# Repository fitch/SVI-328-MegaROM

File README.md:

# SVI-328 MegaROM

## Overview

This is a 1024 kB (8 megabit) ROM cartridge for Spectravideo 328 that fits into a standard SVI-328 game cartridge slot without any hardware modifications.

The implementation is based on Timo Soilamaa's idea on having a CD4060 binary counter chip with a built-in oscillator to control high address lines of a large memory chip. This version exposes a 16 kB window of a larger 1024 kB at time to SVI-328 and changes the window to the next after a while has passed. A more thorough explanation on how it works is found in chapter [The hardware](#the-hardware) and [Cartridge ROM contents and operation](#cartridge-rom-contents-and-operation).

## Contents

This repository contains:
 - The source code for the ROM code (a game launcher) that can be burned into an EPROM memory chip.
 - The schematics and the layout of the PCB, which can be manufactured, for example, using [PCBWay](https://www.pcbway.com).
 - A tool (embedded to the makefile) that packs and chunks games into a format that the game launcher can handle on the device.

## System requirements

The implementation has been tested with macOS Sonoma 14.6.1 and requires the following software to be installed, and found from path when executing the `makefile`:
 - [z88dk version 2.3](https://github.com/z88dk/z88dk) (currently only z88dk-z80asm is used)
 - [openMSX emulator version 20.0](https://openmsx.org) (which should be installed in /Applications/openMSX.app)
 - [Node.js version 22.12.10](https://nodejs.org/en) or newer
 - [zx0 version 2.2](https://github.com/einar-saukas/ZX0)
 - [GNU M4](https://www.gnu.org/software/m4) (it should come with [Xcode](https://apps.apple.com/us/app/xcode/id497799835?mt=12) command line developer tools, tested with version 1.4.6)

## I don't have time to read this all :) 

Follow these instructions to get a version up and running in openMSX emulator.

### Create the ROM metadata

When you have installed the previous programs, get a ready 32 kB ROM image like Frantic Freddy, review [roms/roms.json.example](roms/roms.json.example) and create `roms/roms.json` with the following content:

    [
        {
            "name": "Frantic Freddy",
            "author": "Spectravideo",
            "file": "franticfreddy.rom.32.dat.zx0",
            "type": "rom.32.zx0",
            "jump": "0x000c",
            "crc16": "0x9c06"
        }
    ]

You can place the ROM image to `uncompressed_roms` folder with file name `franticfreddy.rom.32.dat` and then run `./calculate_crc16.sh` to see if the crc16 matches the example above. If it does, you're using the correct ROM image.

### Compress the ROM data

Now compress the ROM image using zx0 with `zx0 franticfreddy.rom.32.dat`. You should see something like this:

```
ZX0 v2.2: Optimal data compressor by Einar Saukas
[...............................................]
File compressed from 32768 to 8363 bytes! (delta 2)
```

Move `franticfreddy.rom.32.dat.zx0` to [roms](roms/) folder.

### Compile and run

Now, create an emulator version of the ROM image with `make emulator`.

Then, use `make run` to run the version in openMSX emulator.

### Load the game

You should now see the game selector on screen. Press A to load the game and then navigate to Memory debugger to do the following (to simulate the changing ROM window):
 - Write 0x01 to address 0x8000
 - Write 0x00 to address 0x8000
 - Write 0x01 to address 0x8000

The game should now load.

# The hardware

The cartridge design in inspired by [Noel Llopis' 32 kB cartridge](https://github.com/llopis/SVI328-ROM-Cartridge) for Spectravideo 328. The physical design, however, differs so that the edge connector is now exactly 40 mm wide making it align with the cartridge slot better.

The cartridge has the following components:
 - J1: A 30 pin edge connector that will fit the Spectravideo 328 cartridge slot
 - U1: An EPROM memory chip 27C080 (a UV EPROM version of the [AT27C080](https://ww1.microchip.com/downloads/en/DeviceDoc/doc0360.pdf)) 1024 kB (8 megabit)
 - U2: A 14-stage ripple-carry binary counter and oscillator chip CD4060 ([CD4060BE](https://www.ti.com/lit/ds/symlink/cd4060b.pdf))
 - R1: A 68 kΩ resistor, R2: A 1 kΩ resistor and C2: A 0.1 μF capacitor to provide the CD4060 1 / ( 2.3 * 0.0000001 F * 68000 Ω) = 63.93861893 Hz frequency to the oscillator, making Q3 go high after 8 clock cycles in ~125 milliseconds which is the rotation speed for the ROM windows
 - C1: A 0.1 μF capacitor acts as the decoupling capacitor to remove common noise and transient conditions

See chapter [Sector rotation](#sector-rotation) for information on how the CD4060 operates with the 27C080.

I recommend using a 32-pin spring socket under the memory chip so that it's easy to detach and attach the EPROMs.

# Cartridge ROM contents and operation

## Sector structure

The 1024 kB ROM memory is divided into 64 16384 byte sections (sectors), which consist of the following main parts:
1. The [loader](asm/loader.asm) (currently 16 bytes)
2. The sector data
3. The sector identifier (one byte, the last one in the sector)

Sector 0 (the first sector) contains the following functionality in the sector data (2.) section:
 - [decompressor](asm/decompressor.asm) which sets up the zx0 decompressor in high RAM (`DZX0_ADDRESS`) and also copies the launcher to high RAM (`LAUNCHER_ADDRESS`, see [makefile](makefile) for the values)
 - [launcher](asm/launcher.asm) which displays the game selector, chooses the right game loader and executes the game loading sequence and starts the game

Other sectors (from 1 to 63) contain the game data. This will be explained in chapter [Game data](#game-data).

## Sector rotation

The 1024 kB of a 27C080 is accessed via address lines A0..A19 (2^20 bytes) the following way:
 - The SVI-328 cartridge connector addressess directly the first A0..A13 (2^14 = 16384) bytes when Cartridge ROM bank (bank xx, when /CART is low) is accessed from memory addressess 0x0000 - 0x3fff.
 - Accessing these addresses will also set /CCS1 line low. This line is used to enable the 27C080 memory chip using /OE (output enable) and /CE (chip enable).
 - The CD4060 counter chip coordinates address lines A14 to A19.

The binary counter starts from 0, when all the Qx lines are low (zero). After 8 clock cycles line Q3 goes high (~125 ms) and sets A14 high (1). This will make the 270C080 address pointer point to the 2nd 16 kB block and so on. Cycling through all the 16 kB sectors takes ~8 seconds in this configuration.

As each of the sectors contain the sector identifier byte (starting from 0x00 in sector 0, continuing as 0x01 in sector 1 and so on), you can always check which sector is visible by reading the memory address 0x3fff (when bank xx is selected by setting /CART low [using the PSG](asm/launcher/psg.asm)).

The ~125 ms rotation speed is based on that then the CPU has enough time to read the 16 kB of sector data and write it to RAM using [FastLDIR](asm/launcher/fast_ldir.asm) memory copying function.

## Boot up procedure

When the SVI-328 is booted up with the cartridge ROM attached, it follows these phases:

1. When a cartridge ROM is attached, /CART is set low and the memory bank mapping the cartridge ROM contents to 0x0000 - 0x7fff is enabled. (However, we will only use the first 16 kB between 0x0000 - 0x3fff, the contents between 0x4000 - 0x7fff are undefined.)
2. The [loader](asm/loader.asm) is visible at memory address 0x0000 (every sector starts with the loader, so it's always visible at this address). The loader starts with `di` and `ld sp, xxxx` instructions which instructs the SVI-328 that we have a valid cartridge ROM attached.
3. The loader waits until sector 0 has passed (not displaying sector 0) and then waits again until sector 0 is visible again. This is to ensure that the CPU will have enough time to copy the launcher from sector 0 to RAM.
4. Next, the [decompressor](asm/decompressor.asm) will copy the zx0 decompressor to end of RAM at address `DZX0_ADDRESS` (so it won't get overwritten later) and also a compressed copy of the [launcher](asm/launcher.asm) to address 0xc000. Then, the launcher is decompressed to address `LAUNCHER_ADDRESS`.
5. At last, the launcher execution is started in RAM at address `LAUNCHER_ADDRESS`.

## Launcher

The [launcher](asm/launcher.asm) consists of the following sections:

1. [Splash screen](asm/launcher/splash.asm) displayed first when the ROM cartridge boots
2. [Game selector](asm/launcher/game_selector.asm), which let's the user choose the game to be loaded
3. [MSX ROM-loader](asm/MSX/LICENSE) initialization, which prepares MSX ROM games to be loaded and converted (when ROM type is MSX, see chapter [Game data](#game-data))
4. Compressed game data copying to RAM ([launcher](asm/launcher.asm), starts from label `.load_another_part:`)
5. Decompression and jumping routines for different game ROM types

# Game data

## Overview

The launcher supports different types of game or applicaton ROM images, these are explained in the next chapters.

`gamedata.js` processes the `roms.json` and outputs corresponding sector data files into `build` directory and also generates `gamedata.asm` to be used for the game launch metadata when building the final ROM.

## cas.8 and cas.16

`cas.8` and `cas.16` are uncompressed 8 kB or 16 kB images based on .cas file data. An example of a typical `cas.16` game is Mass Tael's Spectravideo games like Turboat or SASA.

`gamedata.js` defaults these ROMs to have a jump and load address of `0x8800`, which you can override with `jump` or `load` keys if needed.

The following is an example on how to configure a 16384 byte image to be launched using `roms.json`:

    {
        "name": "SASA",
        "author": "Mass Tael",
        "file": "sasa.cas.16.dat",
        "type": "cas.16",
        "crc16": "0x166f"
    }

## cas.16.zx0

`cas.16.zx0` is a compressed version of the `cas.16` image.

## rom.32.zx0

`rom.32.zx0` is a compressed 32 kB ROM image.

The following is an example on how to configure a 32768 byte image to be launched using `roms.json`:

    {
        "name": "Frantic Freddy",
        "author": "Spectravideo",
        "file": "franticfreddy.rom.32.dat.zx0",
        "type": "rom.32.zx0",
        "jump": "0x000c",
        "crc16": "0x9c06"
    }

In this case, a non-standard jump address of 0x000c is needed in order for the Frantic Freddy ROM code not to switch /CART low again.

## msx.32.pletter

`msx.32.pletter` is a 32 kB MSX ROM packed with Pletter. This is the format the [MSX ROM-loader for SVI-328](asm/MSX/license.txt) uses by default. However, it is recommended to use `msx.32.zx0` as it packs the games smaller.

Note that with this ROM type you need to split the 32 kB ROM into two 16 kB parts and pack them individually. The following is an example on how to configure a 32768 byte image to be launched using `roms.json`:

    {
        "name": "Arkanoid",
        "author": "Taito",
        "files": [
            "arkanoid.msx.32.part1.dat.pletter",
            "arkanoid.msx.32.part2.dat.pletter"
        ],
        "type": "msx.32.zx0"
    }

## msx.32.zx0

'msx.32.zx0' is a 32 kB MSX ROM packed with ZX0. It is required to split the 32 kB ROM into two 16 kB pieces and then packing them. Please use the script [split_roms.sh](scripts/split_roms.sh) to split the original ROM and pack the pieces with ZX0.

The following is an example on how to configure a 32768 byte MSX image to be launched using `roms.json`:

    {
        "name": "Zanac",
        "author": "Compile",
        "files": [
            "zanac.msx.32.part1.dat.zx0",
            "zanac.msx.32.part2.dat.zx0"
        ],
        "type": "msx.32.zx0"
    }

## msx.16.zx0

'msx.16.zx0' is a 16 kB MSX ROM packed with ZX0. It can be supplied in single file.

The following is an example on how to configure a 16384 byte MSX image to be launched using `roms.json`:

    {
        "name": "Boulder Dash",
        "author": "First Star Software",
        "file": "boulderdash.msx.16.dat.zx0",
        "type": "msx.16.zx0"
    }

## rom.48.zx0

'rom.48.zx0' is a SVI-328 game that has 48 kB size. Note that this is not a ROM image as SVI-328 48 kB ROMs are virtuallu non-existent and the physical ROM cartridges operate a little differently than 32 kB ROMs.

Compiling the production ROM with `make production` shows the maximum compressed image file size that can be loaded in single part:

`Maximum compressed ROM size in this build: 31898`

If the compressed image exceeds that size, you need to split the image into parts using [split_roms.sh](scripts/split_roms.sh) script.

Here are examples of games with compressed size less than ~31k and larger:

    {
        "name": "Gunfright",
        "author": "Ultimate Play the Game",
        "file": "gunfright.rom.48.dat.zx0",
        "type": "rom.48.zx0"
    }

    {
        "name": "Knightmare",
        "author": "Konami",
        "files": [
            "knightmare.rom.48.part1.dat.zx0",
            "knightmare.rom.48.part2.dat.zx0"
        ],
        "type": "rom.48.zx0"
    }

## cas.len.zx0

'cas.len.zx0' is a format which has a variable size (other than 8 or 16 kB).

In this ROM type, you need to supply the uncompressed game length using `length` parameter.

    {
        "name": "Hero",
        "author": "Activision",
        "file": "hero.cas.len.dat.zx0",
        "type": "cas.len.zx0",
        "crc16": "0x0ecb",
        "load": "0x8000",
        "jump": "0x8000",
        "length": "17153"
    }

# Compiling the production version

To compile the production version of the ROM cartridge image, please use `make production`. 

If the build prosess reports an error (see below) about modifying `SECTOR0_START`, you need to supply a larger value to the `makefile`.

    z88dk-z80asm -o=build/sector0.bin -DSECTOR0_START=9100 -DLAUNCHER_ADDRESS=0x8001               -DDZX0_ADDRESS=65468                    -m -l -b -DROM_ID=0 build/rom1024.asm -I=asm
    build/rom1024.asm:24: error: integer range: -$3e6
    ^---- defs SECTOR0_START-$, 0xff ; If this fails, increase SECTOR0_START in makefile
        ^---- defs SECTOR0_START-$,255

If you supplied a value large enough, the build process successfully completes and suggests the actual value:

    Magic number (use this in makefile): 10095
    Maximum compressed ROM size in this build: 31943
    1024 kB version compiled (release/cart1024.rom)

To optimize the ROM cartridge usage you should use the provided Magic number as `SECTOR0_START` value. In some cases, even if you supply the exact magic number, the build process still can crash with a following type of error:

    build/rom1024.asm:24: error: integer range: -1
    ^---- defs SECTOR0_START-$, 0xff ; If this fails, increase SECTOR0_START in makefile
        ^---- defs SECTOR0_START-$,255

Then, just increase `SECTOR0_START` with one or two, rebuild and keep doing this until it successfully builds the ROM image. As supplying a different value will change the contents of the launcher image, and once it is compressed with different contents, the resulting image lenght may vary. This makes it impossible to know the resulting compressed launcher image size in beforehand.

You will find the resulting ROM image from `release/cart1024.rom`.

# Burning the EPROM

To burn the ROM image to an EPROM, you can use [minipro](https://formulae.brew.sh/formula/minipro) version 0.7.2 on macOS. Use the following command with AT27C080 with DIP32 pins:

```
minipro -p AT27C080@DIP32 -w cart1024.rom
```

For the EPROM burner, I'm suggesting a [TL866II Plus](https://www.amazon.de/dp/B07KM3J7CZ) programmer. To erase the UV EPROMS you can use a [UV EPROM eraser](https://www.amazon.de/-/en/dp/B000M5AJ8Q).

I had to update the programmer firmware first with a Windows machine in order to get it to work on macOS. See the details of the minipro output below:

```
Found T48 01.1.31 (0x11f)
Warning: T48 support is experimental!
Device code: 44A13469
Serial code: VTQRRFJKXR60YE8R9I6Y4274

VPP=13V, VDD=6.5V, VCC=5V, Pulse=50us
Chip ID: 0x1E8A  OK
Writing Code...  257.18Sec  OK
Reading Code...  7.25Sec  OK
Verification OK
```

# Special thanks

This cartridge ROM is based on Timo Soilamaa's idea on using the binary counter chip as the address mapper. I would like to thank Timo also on providing valuable information about the Spectravideo 328 hardware, some hands-on testing and advice on using the MSX ROM-loader for SVI-328.

The PCB design is inspired by [Noel Llopis' SVI-328 32 kB cartridge](https://github.com/llopis/SVI328-ROM-Cartridge) project.

I've also gotten useful information from Duncan Morrison about .CAS files and the information about 32 kB and 64 kB ROMs from Tony Cruise.

# Embedded source code and their license

For license of using this source code and hardware, please see [LICENSE](LICENSE). 

The ROM code includes [EXEROM](asm/MSX/EXEROM) binary from MSX ROM-loader for SVI-328 version 1.5 by NYYRIKKI. See the licensing information from [here](asm/MSX/LICENSE).

Also, the launcher uses [ZX0 "Standard" decompressor](asm/ZX0/dzx0_standard.asm) by Einar Saukas & Urusergi. See the licensing information from [here](asm/ZX0/LICENSE).

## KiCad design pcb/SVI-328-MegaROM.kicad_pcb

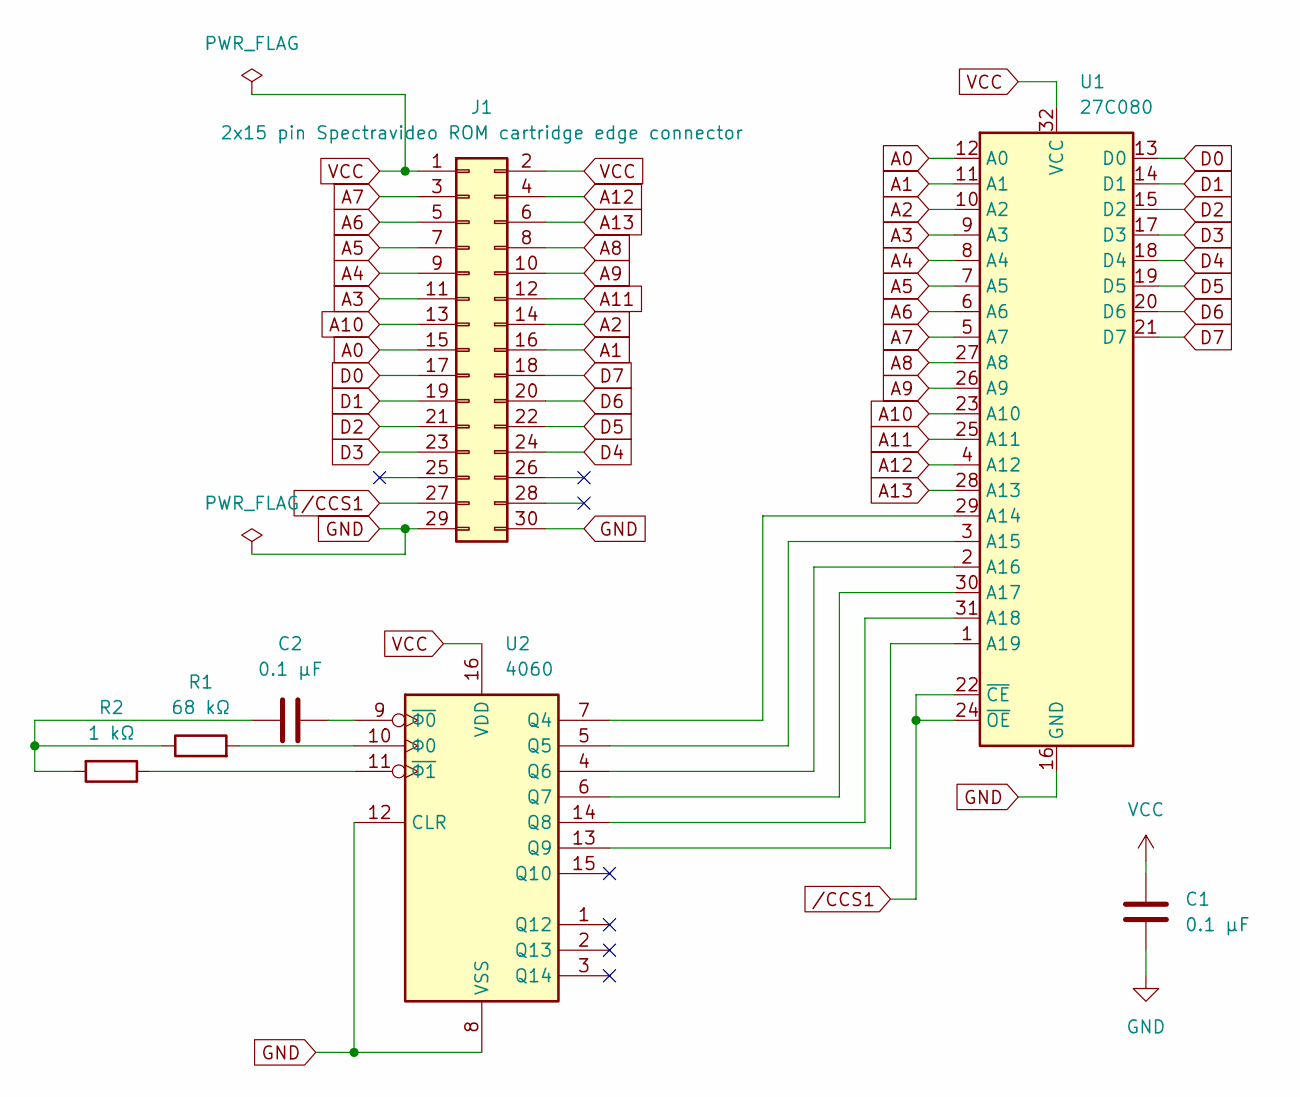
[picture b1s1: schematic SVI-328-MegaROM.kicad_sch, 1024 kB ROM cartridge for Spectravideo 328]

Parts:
C1, C2: 0.1 μF; C_Disc_D4.3mm_W1.9mm_P5.00mm
J1: 2x15 pin Spectravideo ROM cartridge edge connector; ROM cartridge edge connector
R1: 68 kΩ; R_Axial_DIN0207_L6.3mm_D2.5mm_P7.62mm_Horizontal
R2: 1 kΩ; R_Axial_DIN0207_L6.3mm_D2.5mm_P7.62mm_Horizontal
U1: 27C080; DIP-32_W15.24mm
U2: 4060; DIP-16_W7.62mm

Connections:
A0: J1.15, U1.12 (A0)
A1: J1.16, U1.11 (A1)
A2: J1.14, U1.10 (A2)
A3: J1.11, U1.9 (A3)
A4: J1.9, U1.8 (A4)
A5: J1.7, U1.7 (A5)
A6: J1.5, U1.6 (A6)
A7: J1.3, U1.5 (A7)
A8: J1.8, U1.27 (A8)
A9: J1.10, U1.26 (A9)
A10: J1.13, U1.23 (A10)
A11: J1.12, U1.25 (A11)
A12: J1.4, U1.4 (A12)
A13: J1.6, U1.28 (A13)
D0: J1.17, U1.13 (D0)
D1: J1.19, U1.14 (D1)
D2: J1.21, U1.15 (D2)
D3: J1.23, U1.17 (D3)
D4: J1.24, U1.18 (D4)
D5: J1.22, U1.19 (D5)
D6: J1.20, U1.20 (D6)
D7: J1.18, U1.21 (D7)
GND: C1.2, J1.29, J1.30, U1.16 (GND), U2.8 (VSS), U2.12 (CLR)
unnamed: C2.1, R1.1, R2.2
unnamed: U1.29 (A14), U2.7 (Q4)
unnamed: U1.3 (A15), U2.5 (Q5)
unnamed: U1.2 (A16), U2.4 (Q6)
unnamed: U1.30 (A17), U2.6 (Q7)
unnamed: U1.31 (A18), U2.14 (Q8)
unnamed: U1.1 (A19), U2.13 (Q9)
unnamed: C2.2, U2.9 (~Φ0)
unnamed: R2.1, U2.11 (~Φ1)
unnamed: R1.2, U2.10 (Φ0)
VCC: C1.1, J1.1, J1.2, U1.32 (VCC), U2.16 (VDD)
/CCS1: J1.27, U1.22 (~CE), U1.24 (~OE)

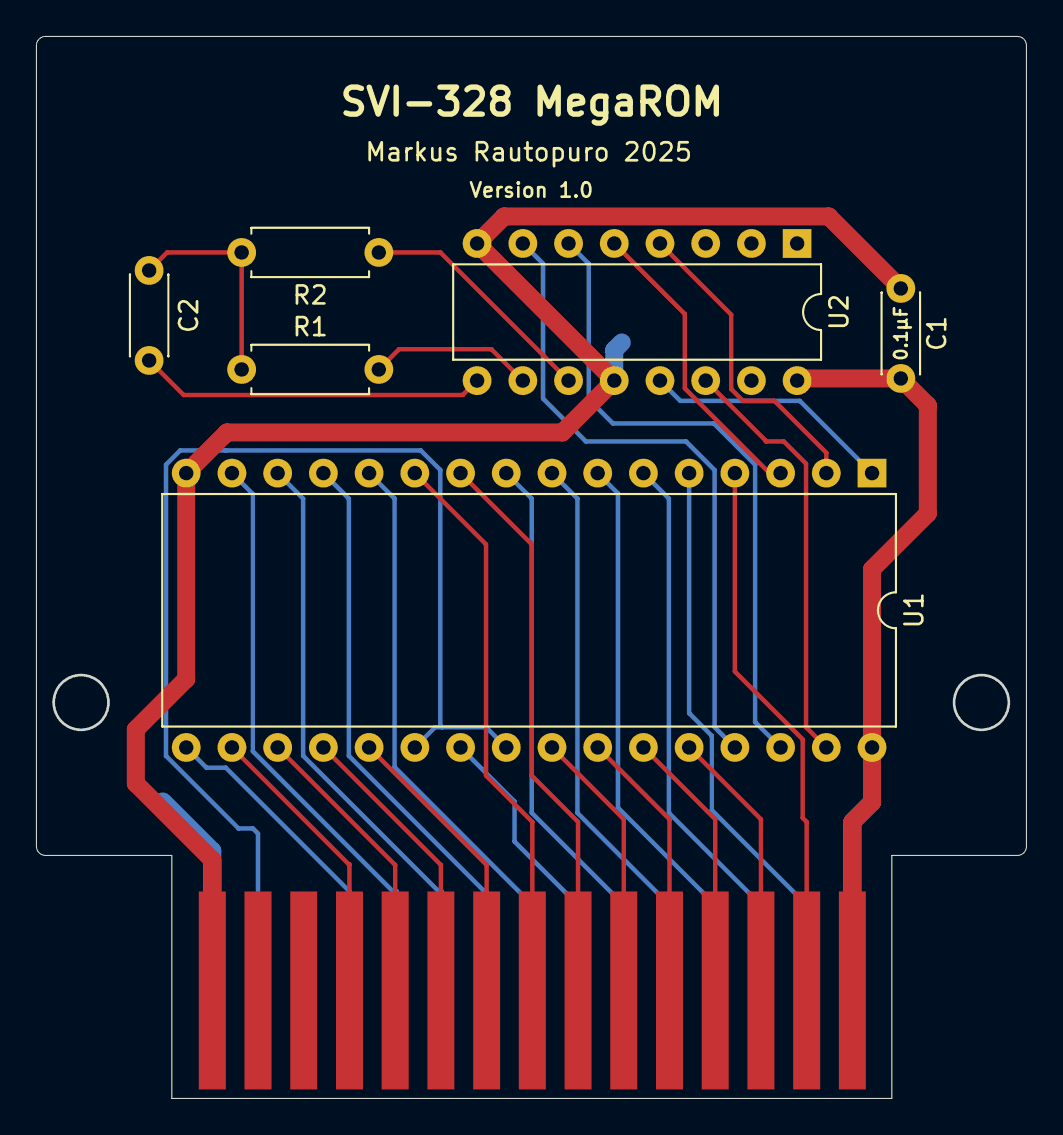
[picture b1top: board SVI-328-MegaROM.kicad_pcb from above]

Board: 2 copper layers, 55.0 x 59.0 mm, 7 parts (0 on the bottom side), 35 nets.

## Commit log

2025-01-23 Version 1.0
2025-02-20 Add a feature to generate a game list, fix some labels in the assembly files, rename simulator references to emulator and add more information to README.md

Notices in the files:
README.md:
Embedded source code and their license:
For license of using this source code and hardware, please see [LICENSE](LICENSE).
The ROM code includes [EXEROM](asm/MSX/EXEROM) binary from MSX ROM-loader for SVI-328 version 1.5 by NYYRIKKI. See the licensing information from [here](asm/MSX/LICENSE).
Also, the launcher uses [ZX0 "Standard" decompressor](asm/ZX0/dzx0_standard.asm) by Einar Saukas & Urusergi. See the licensing information from [here](asm/ZX0/LICENSE).
